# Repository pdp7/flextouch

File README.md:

# flextouch
OSH Park Flex PCB touch test

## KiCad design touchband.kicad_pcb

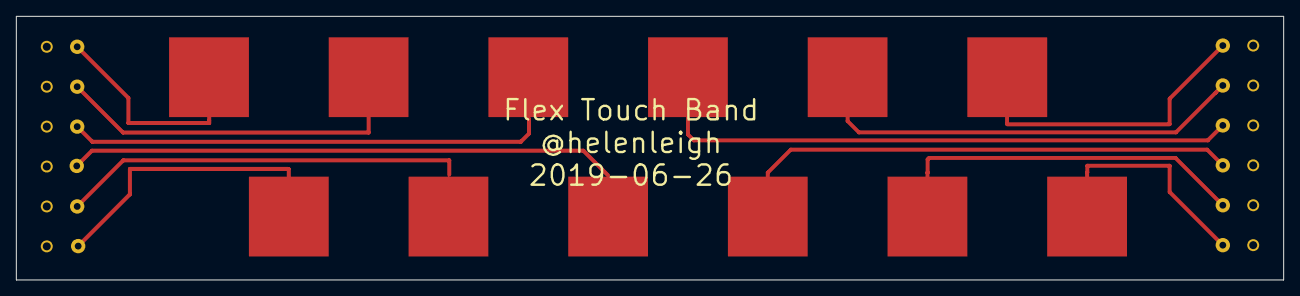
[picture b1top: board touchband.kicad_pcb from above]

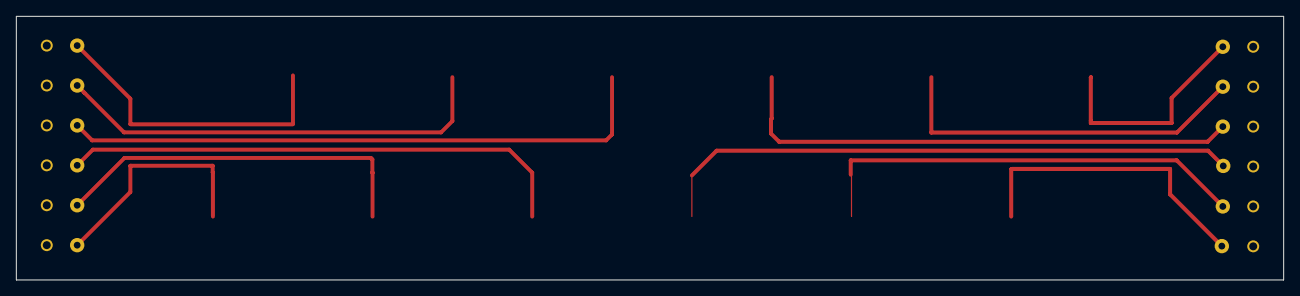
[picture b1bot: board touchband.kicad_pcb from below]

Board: 2 copper layers, 158.8 x 33.0 mm, 36 parts (12 on the bottom side), 12 nets.

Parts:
J1, J8, J9, J10, J11, J12, J13, J14, J15, J16, J17, J18: Conn_01x01_Female; hole30AWG
J2, J3, J5, J6, J7, J19, J20, J21, J22, J23, J24: Conn_01x01_Female; strain30AWG
J4: \; strain30AWG
TP1, TP2, TP3, TP4, TP5, TP6, TP7, TP8, TP9, TP10, TP11, TP12: TestPoint; Touch_Pad_10x10mm

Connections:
unnamed: J1.1, TP1.1
unnamed: J8.1, TP2.1
unnamed: J9.1, TP3.1
unnamed: J10.1, TP4.1
unnamed: J11.1, TP5.1
unnamed: J12.1, TP6.1
unnamed: J13.1, TP7.1
unnamed: J14.1, TP8.1
unnamed: J15.1, TP9.1
unnamed: J16.1, TP10.1
unnamed: J17.1, TP11.1
unnamed: J18.1, TP12.1

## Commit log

2019-06-17 initial test board
2019-06-18 initial 12 touch band design
2019-06-27 finalize traces and add silk text
2019-06-27 final amends to test touch band
2019-12-07 Add teardrops to vias and pads using plugin
    The Teardrop action plugin from:
    https://github.com/NilujePerchut/kicad_scripts/tree/master/teardrops
2019-12-09 add rounded touch with teardrop
    Using KiCad teardrop action plugin
    https://github.com/NilujePerchut/kicad_scripts/tree/master/teardrops
2019-12-21 add round pads to flex touch band
2019-12-21 start re-routing flex touch board
2019-12-26 add rounded tracks using plugin
2019-12-26 improve round traces with plugin
2019-12-28 update round tracks
2019-12-31 add more round tracks
2020-01-04 final version of flextouch with round tracks
2020-01-25 remove errant teardrop on the silk layer
